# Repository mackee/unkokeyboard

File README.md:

# Cool Poop Keyboard

The Cool Poop Keyboard is a too-small keyboard.

This keyboard has only 4 keys and 4 full-color LEDs.

It uses an ATTiny84 with [micronucleus](https://github.com/micronucleus/mirconucleus) firmware.

This product made for distributing at [The Techbook fest 7th](https://techbookfest.org/event/tbf07).

Following japanese text is a build guide for customer.

# かっこいいうんこキーボード

この文章は技術書典7などで頒布した「かっこいいうんこキーボード」の取扱説明書です。

## この文章で知れること

- 「かっこいいうんこキーボード」の組み立て方
- 「かっこいいうんこキーボード」のファームウェアのカスタマイズ方法

## 組み立て方

### 部品

|名前|数|備考|
|:---|:---|---|
|PCB|1枚||
|プレート|1枚||
|キースイッチ|4個|赤 or 白 or 茶が4個入っています|
|キーキャップ|4個||
|スペーサー|4個||

### 組み立て
1. PCBにスペーサーを取り付ける。

2. プレートを取り付けて、裏返す。

3. キースイッチを付ける。

4. キーキャップを付けて完成。

## ファームウェアのカスタマイズ方法

### 必要なもの

- [PlatformIO](https://platformio.org/)
- Windowsの場合は[Digisparkのドライバー](https://github.com/digistump/DigistumpArduino/releases/download/1.6.7/Digistump.Drivers.zip)のインストールが必要です
  - また、`make`および`patch`が使える環境が必要です

### ファームウェアの書き込み手順

#### 1. このリポジトリのダウンロード

`git clone`やzipファイルのdownload linkからこのリポジトリのソースコードをダウンロードします。

#### 2. 書き込み環境のセットアップ

`make`コマンドを実行できるCLI環境で1でダウンロードし、展開したディレクトリに移動します。そして、そのディレクトリで以下のコマンドを実行します。

```console
$ make init
```

途中にコンパイルエラーが出ますが、その後にコンパイルエラーを解消するためのパッチが自動で適用されます。

#### 3. ファームウェアの書き込み

以下のコマンドで、「かっこいいうんこキーボード」へのファームウェアの書き込みが実行されます。

```console
$ make upload
```

`> Please plug in the device ...` というメッセージが表示された、「かっこいいうんこキーボード」をUSBケーブルで接続してください。もし、接続したまま実行した場合は、一度抜いてからもう一度挿してください。

`>> Micronucleus done. Thank you!` というメッセージが表示されたら成功です。

### キーのカスタマイズ

キー配置の情報は、`src/Keyboard.ino`に記述されています。

それぞれのキーを`A`, `B`, `C`, `D`に変更する場合は、

```diff
--- a/src/Keyboard.ino
+++ b/src/Keyboard.ino
@@ -8,7 +8,7 @@ WS2812 LED(NEOPIXELS_NUM);
 cRGB value;

 uint8_t keys[] = {9, 8, 7, 3};
-byte keymaps[] = {KEY_U, KEY_N, KEY_K, KEY_O};
+byte keymaps[] = {KEY_A, KEY_B, KEY_C, KEY_D};

 void setup() {
   LED.setOutput(NEOPIXEL_PIN);
```

というように変更し、保存した後に`make upload`を実行して書き込みます。

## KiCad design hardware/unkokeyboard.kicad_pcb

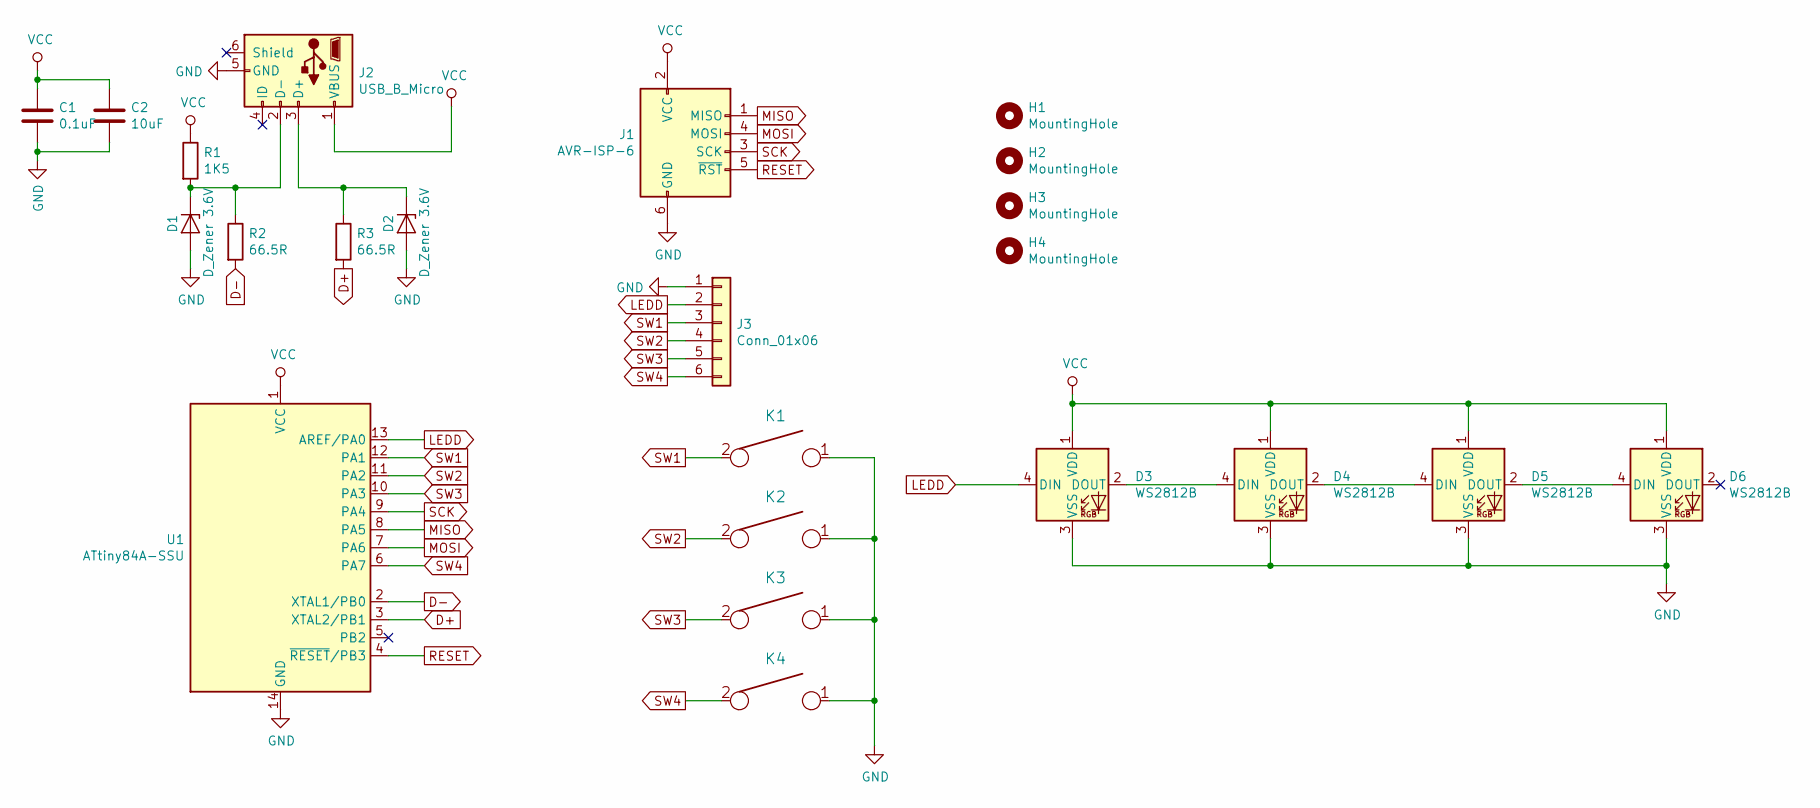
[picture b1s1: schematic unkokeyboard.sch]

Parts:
C1: 0.1uF; C_1608
C2: 10uF; C_1608
D1, D2: D_Zener 3.6V; D_SOD-323_HandSoldering
D3, D4, D5, D6: WS2812B; WS2812B-2020
H1, H2, H3, H4: MountingHole; MountingHole_2.5mm
J1: AVR-ISP-6; PinHeader_1x06_P2.54mm_Vertical
J2: USB_B_Micro; USB_microB
J3: Conn_01x06; PinHeader_1x06_P2.54mm_Vertical
K1, K2, K3, K4: KEYSW; PG1350_socket
R1: 1K5; R_0603_HandSoldering
R2, R3: 66.5R; R_0603_HandSoldering
U1: ATtiny84A-SSU; SOIC-14_3.9x8.7mm_Pitch1.27mm

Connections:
D+: R3.2, U1.3 (XTAL2/PB1)
D-: R2.2, U1.2 (XTAL1/PB0)
GND: C1.2, C2.2, D1.2 (A), D2.2 (A), D3.3 (VSS), D4.3 (VSS), D5.3 (VSS), D6.3 (VSS), J1.6 (GND), J2.5 (GND), J3.1, K1.1, K2.1, K3.1, K4.1, U1.14 (GND)
LEDD: D3.4 (DIN), J3.2, U1.13 (AREF/PA0)
MISO: J1.1 (MISO), U1.8 (PA5)
MOSI: J1.4 (MOSI), U1.7 (PA6)
unnamed: D1.1 (K), J2.2 (D-), R1.2, R2.1
unnamed: D2.1 (K), J2.3 (D+), R3.1
unnamed: D3.2 (DOUT), D4.4 (DIN)
unnamed: D4.2 (DOUT), D5.4 (DIN)
unnamed: D5.2 (DOUT), D6.4 (DIN)
RESET: J1.5 (~RST), U1.4 (~RESET~/PB3)
SCK: J1.3 (SCK), U1.9 (PA4)
SW1: J3.3, K1.2, U1.12 (PA1)
SW2: J3.4, K2.2, U1.11 (PA2)
SW3: J3.5, K3.2, U1.10 (PA3)
SW4: J3.6, K4.2, U1.6 (PA7)
VCC: C1.1, C2.1, D3.1 (VDD), D4.1 (VDD), D5.1 (VDD), D6.1 (VDD), J1.2 (VCC), J2.1 (VBUS), R1.1, U1.1 (VCC)

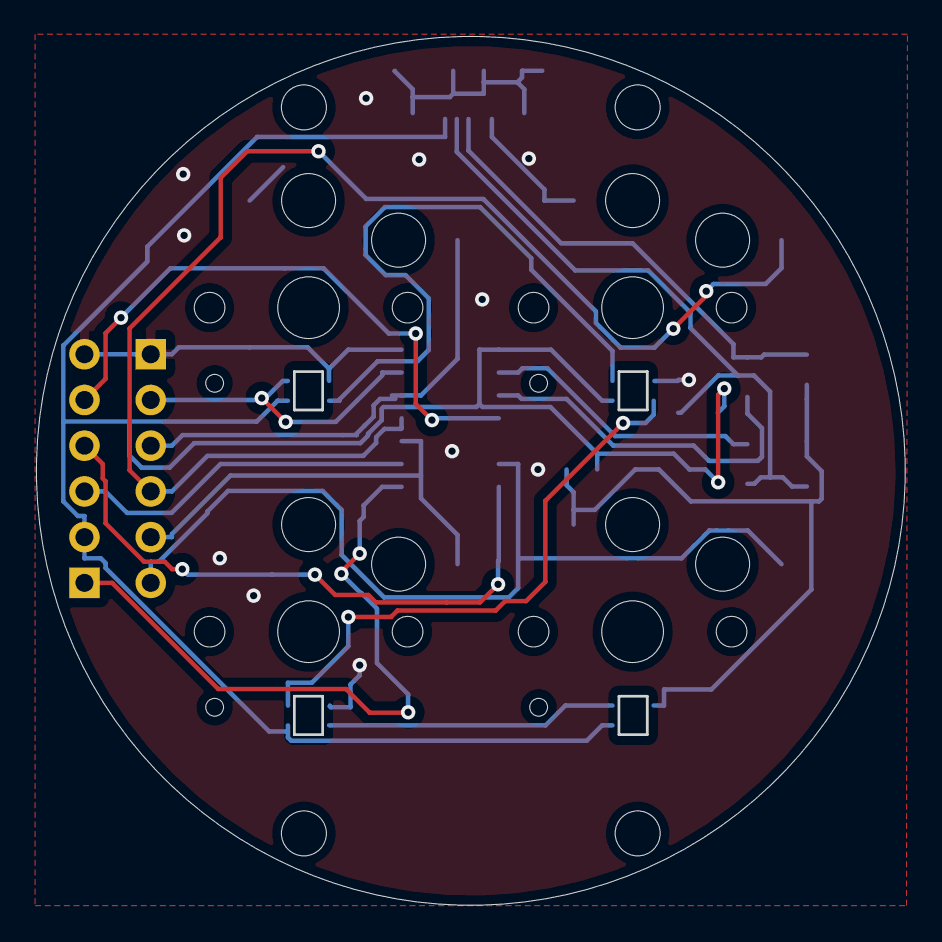
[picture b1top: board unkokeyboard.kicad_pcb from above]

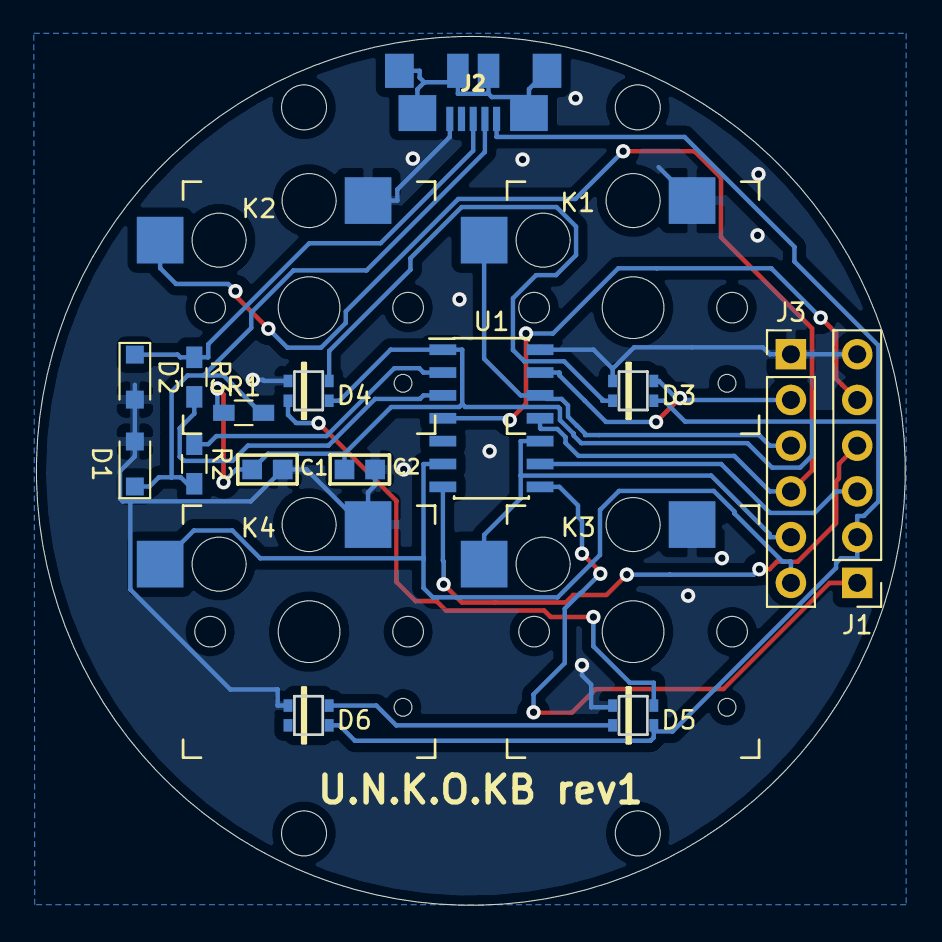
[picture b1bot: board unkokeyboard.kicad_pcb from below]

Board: 2 copper layers, 48.2 x 48.2 mm, 23 parts (11 on the bottom side), 18 nets.

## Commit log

2019-09-21 組み立て方追加
2019-09-29 add pcb
2019-09-29 add english detials
2019-09-29 fix images path
